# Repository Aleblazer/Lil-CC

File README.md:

# Lil-CC: A C to C interconnect for split keyboards. (thinner version for surface mount only)

Based off of the Unified-Daughterboard project, this surface mount board allows you to add USB C-C interconnects on your split keyboard projects, minimizing the risk of MCU damage over standard TRRS cables. Could also be used as a surface mount USB MCU connection, but has not be tested in that capacity.

## Credits
- [Gondolindrim](https://github.com/Gondolindrim)
- [hineybush](https://hineybush.com/)
- [ai03](https://ai03.com/)
- [GEON](https://geon.works/)
- [Sleepdealer](https://sleepdealer.xyz)
- [Xelus](https://xelus.me)
- [James (AKB)](https://alchemistkeyboards.com/)
- [kkatano](https://github.com/kkatano)
- [ToastyStoemp](https://vwolf.be)
- [Upas](https://cannonkeys.com)

C3 Unified:
- [Wilba](https://wilba.tech)
- Xondat
- [aeryxz](https://github.com/aeryxz)
- [Maximillian](https://github.com/Maximillian)

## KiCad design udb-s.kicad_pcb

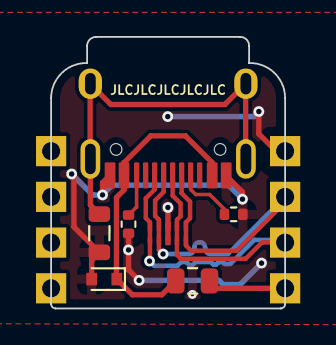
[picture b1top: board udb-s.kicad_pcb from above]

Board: 2 copper layers, 13.0 x 15.1 mm, 9 parts (0 on the bottom side), 8 nets.

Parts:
D1: ESD5Z5V0; D_SOD-523
F1: SMD0805-050-16V; Fuse_0805_2012Metric
FB1: GZ2012D601TF; L_0805_2012Metric
J1: TYPE-C-31-M-12; HRO-TYPE-C-31-M-12-Assembly
J2, J3: Conn_01x04; Castellated2.54-01x04
R1, R2: 5.1k; R_0402_1005Metric
U1: TPD4E05U06DQAR; USON-10_2.5x1.0mm_P0.5mm

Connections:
5V: F1.2, J2.1
D+: J1.A6 (D+), J1.B6 (D+), J2.2, U1.1 (IO1), U1.4 (D2+), U1.7 (NC), U1.10 (NC)
D-: J1.A7 (D-), J1.B7 (D-), J2.3, U1.2 (IO2), U1.5 (D2-), U1.6 (NC), U1.9 (NC)
GND: D1.2 (A2), FB1.2, J1.A1 (GND), J1.B1 (GND), J2.4, R1.1, R2.2, U1.3 (GND), U1.8 (GND)
GNDPWR: FB1.1, J1.S1 (SHIELD)
unnamed: J1.A5 (CC1), R1.2
unnamed: J1.B5 (CC2), R2.1
VBUS: D1.1 (A1), F1.1, J1.A4 (VBUS), J1.B4 (VBUS)

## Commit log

2023-04-04 Lil-CC init upload
2023-08-03 Added thin version
2024-10-30 Fuse Footprint update
2024-10-30 Fuse footprint update.
2025-04-29 JLC Assembly Update
    Added updated JLC files and updated the project to KiCad 9, these have not been tested yet, so use at your own risk.
2025-04-29 Small board fix and update.
2025-04-30 Fix inconsistent alignment
